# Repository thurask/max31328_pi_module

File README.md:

# MAX31328-based RTC module for Raspberry Pi

## Rationale
The MAX31328 is the updated (and cheaper!) refresh of the venerable DS3231 RTC chip, although there's very few MAX31328 based time modules for Pi, and even fewer in the tiny footprint of the usual Aliexpress special RTC module. Also I wanted to learn KiCAD some more. :)

## Installation
In your /boot/firmware/config.txt file add the line ```dtoverlay=i2c-rtc,ds3231``` at the end, then turn the Pi off. Plug the 5 pin header into GPIO pins 1, 3, 5, 7 and 9 (+3V3, SDA, SDL, not connected, GND, respectively), then turn it back on. If it worked, you should see something happen when running ``hwclock -w``. Since the MAX31328 is a drop-in replacement for the DS3231 you may notice that these instructions are the same as any RTC module using that particular chip.

## Building the PCB
Import project files into KiCad 10 and export to your PCB manufacturing service of choice, or just use the files in the grbl subfolder.

## BOM
1. MAX31328: the star of the show, accept no substitutes. 
2. Battery holder: Keystone Electronics 3030. This takes CR927 or CR1025 non-rechargeable 3V lithium coin cells. Not as compact as the RTC modules with the bare tabs soldered on the board, but you can replace the battery on this one without breaking out the soldering iron.
3. I2C pullups: two 4.7 kΩ 0805 resistors, although I think you can get away with using the Pi's built in I2C pullups. Still, belt and braces.
4. Decoupling caps: two pairs of 1μF + 0.1μF 0805 capacitors, one pair for VCC (the Pi, closer to the GND pin) and the other pair for VBATT (the battery, closer to the 3V3 pin).
5. Pin headers: right angle or straight, just as long as it'll fit onto the Pi's GPIO pins. Standard 2.54mm pitch.

## Contributing
Feel free to do what you like with this; build it, change it, fix it, sell it, whatever. If you do make improvements it'd be super cool to make those publicly available.

## License
[CC0-1.0](LICENSE)

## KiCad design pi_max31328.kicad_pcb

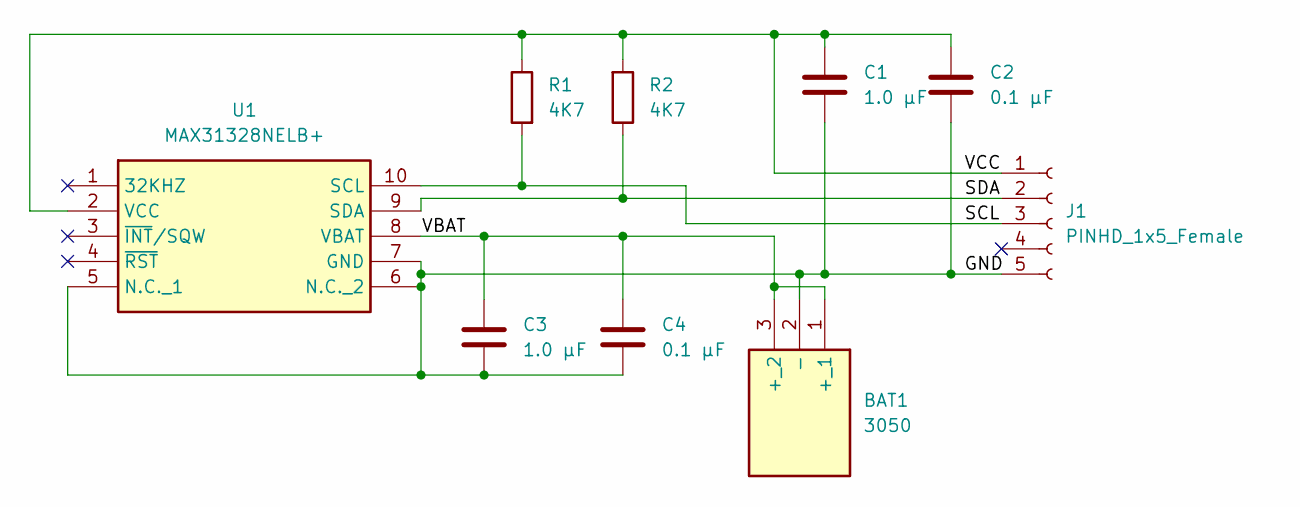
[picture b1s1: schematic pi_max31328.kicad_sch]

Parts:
BAT1: 3050; Mouser Part Number 534-3050
C1, C3: 1.0 μF; C_0805_2012Metric
C2, C4: 0.1 μF; C_0805_2012Metric
J1: PINHD_1x5_Female; PinSocket_1x05_P2.54mm_Vertical
R1, R2: 4K7; R_0805_2012Metric
U1: MAX31328NELB+; MAX31328NELB; Mouser Part Number 700-MAX31328NELB+

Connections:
/GND: BAT1.2 (-), C1.2, C2.2, C3.2, C4.2, J1.5, U1.5 (N.C._1), U1.6 (N.C._2), U1.7 (GND)
/SCL: J1.3, R1.1, U1.10 (SCL)
/SDA: J1.2, R2.2, U1.9 (SDA)
/VBAT: BAT1.1 (+_1), BAT1.3 (+_2), C3.1, C4.1, U1.8 (VBAT)
/VCC: C1.1, C2.1, J1.1, R1.2, R2.1, U1.2 (VCC)

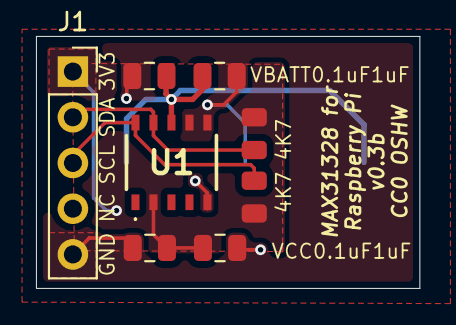
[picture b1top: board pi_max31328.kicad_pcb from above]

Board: 2 copper layers, 21.3 x 14.0 mm, 9 parts (1 on the bottom side), 5 nets.

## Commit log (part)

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2024-09-09 v0.2
